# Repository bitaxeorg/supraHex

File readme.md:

> Closed Source is Antithetical to Bitcoin

# Presenting: The supraHex
supraHex is a follow on to the [bitaxe](https://github.com/skot/bitaxe) that incorporates six BM1368 ASICs from the Antminer S21

## Goals
- **Standalone**: can mine directly to your pool over WiFi. No External computer needed.
- **Embedded**: low cost, low maintenance, high availability, high reliability, low power.
- **ASIC**: based on the very efficient BM1368 from Bitmain.
- **Versatile**: solo/pool mining, autotune power/heat/efficiency.
- **Open Source**: All design files are provided.

## Features
- **ESP32-S3-WROOM-1** wifi microcontroller on board
- **TI TPS546D24ARVFR** buck regulator steps down the 12V input to power the chain of BM1368
- **TMP1075** measures inlet and outlet PCB temperature.
- **Microchip EMC2302** Controls dual fans
- Header for optional status LCD
- BAP (Bitaxe Accesory Port)
- ASIC Chip temperature directly from the ASIC's

## BM1368
- The BM1368 is a undocumented SHA256 mining ASIC from Bitmain. It's mostly used in the Antminer S21
- Bitmain claims the BM1368 has 17.5 W/TH efficiency
- The BM1368 is available (new) for around $20~29 each.

## Current Status
- v701 hardware is working! Hash rate is fluctuating between 4 TH/s and 4.2 TH/s.
- Power draw is around 75W @12V.
- ESP32 miner firmware will configure the power supply to run at the proper voltage.
- This is an _advanced_ build! If you don't have experience building boards, you should probably go build a single ASIC bitaxe first to get the technique down.

## Revision List
- V701 is the current working version of this board.  If you want to build this, pull down this git tag.

## Hardware
- [BM1368 from NBTC](https://www.nbtcminer.com/shop/miner-parts/miner-chip/new-bm1368-bm1368pb-for-antminer-s21-t21-hdyro/). The `PB`Variant seems to work fine.
- [Heatsink](https://www.aliexpress.us/item/3256805608902122.html) 90mm long variant. This will need to have threaded M3 mounting holes added. See the KiCad board file for the pattern
- [Fans](https://www.amazon.com/Noctua-NF-A8-PWM-Premium-Quiet/dp/B00NEMG62M) At least one 80x80mm 12V 4-pin fan. Like the Noctua NF-A8 PWM. Possibly two.
- [Enclosure](https://www.aliexpress.us/item/3256806064761702.html) (several sellers) 130mm long variant. The supraHex needs to be run inside an enclosure to force air through the heatsink and effectively cool the BM1368s
- All of the parts on the board are listed in the KiCad BOM

## Software
- [ESP-Miner-Multichip](https://github.com/bitaxeorg/esp-miner-multichip) is still being updated to support multiple ASICs

## Power Supply Requirements
- supraHex takes 12V DC input via screw terminals. Power supply should be capable of 100W
  - This [120W Brick](https://www.amazon.com/gp/product/B07PWZQ33N) technically works, but gets a little warmer than it should. You'll need to change the end.
  - 12V 15A 110V AliExpress [Bare PSU](https://www.aliexpress.us/item/3256805439916551.html)

## Building
- Check out [building.md](building.md) for PCB ordering tips
- Check out [assembly.md](assembly.md) for assembly tips

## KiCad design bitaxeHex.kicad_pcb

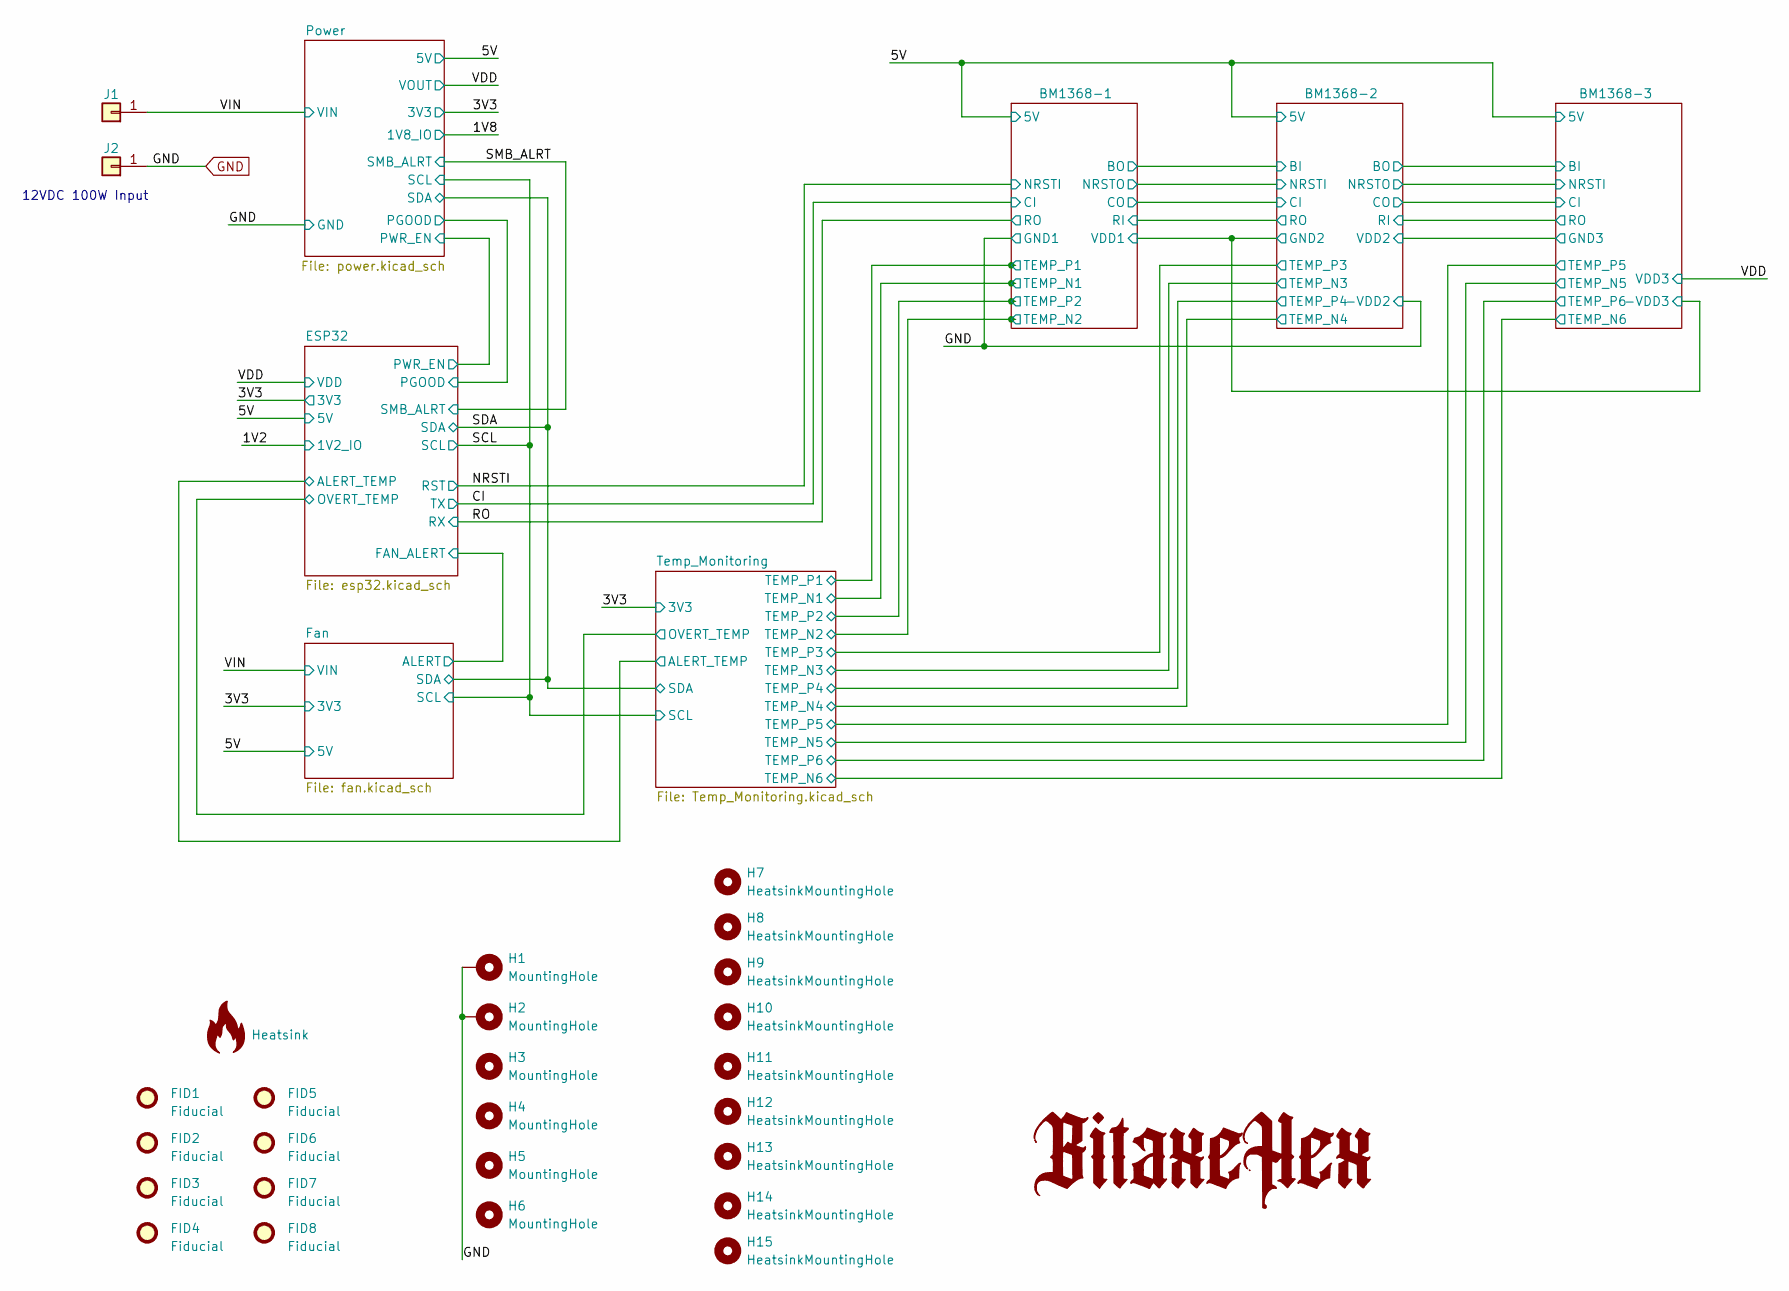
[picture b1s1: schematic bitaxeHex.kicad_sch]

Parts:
FID1, FID2, FID3, FID4, FID5, FID6, FID7, FID8: Fiducial; Fiducial_1mm_Mask2mm
H1, H2, H3, H4, H5, H6: MountingHole; MountingHole_3mm_Pad_Via
H7, H8, H9, H10, H11, H12, H13, H14, H15: HeatsinkMountingHole; 3.1mm_mounting
HS1: Heatsink; hex-heatsink
J1, J2: Screw Terminal; 7771-screw-terminal; PARTNO 36-7771

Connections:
/VIN: J1.1; also elsewhere on the board
GND: H1.1, H2.1, J2.1; also elsewhere on the board

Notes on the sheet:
12VDC 100W Input

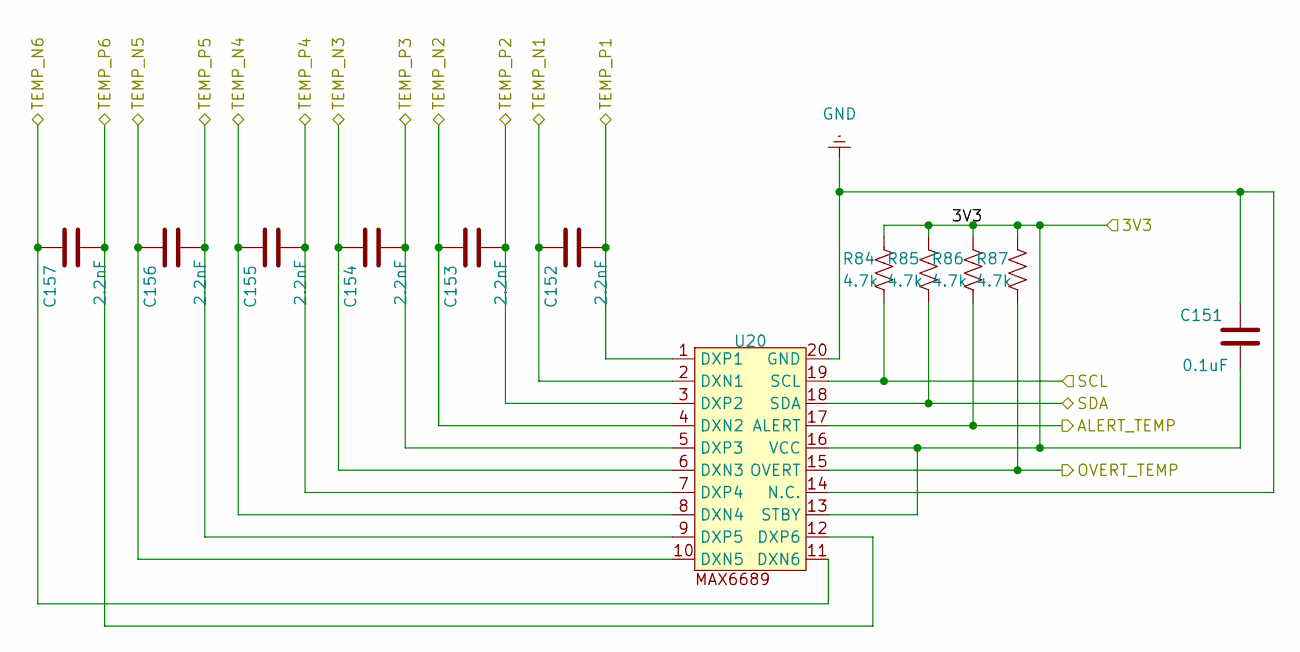
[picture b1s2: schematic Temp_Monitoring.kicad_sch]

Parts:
C151: 0.1uF; C_0402_1005Metric; PARTNO KGM05AR71C104KH
C152, C153, C154, C155, C156, C157: 2.2nF; C_0402_1005Metric; PARTNO CC0402KRX7R9BB222
R84, R85, R86, R87: 4.7k; R_0402_1005Metric; PARTNO RT0402BRD074K7L
U20: MAX6689UP9A+; PARTNO MAX6689UP9A+

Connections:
/3V3: C151.1, R84.2, R85.2, R86.2, R87.2, U20.13 (STBY), U20.16 (VCC); also elsewhere on the board
/BM1368-1/TEMP_N1: C152.2, U20.2 (DXN1); also elsewhere on the board
/BM1368-1/TEMP_N2: C153.2, U20.4 (DXN2); also elsewhere on the board
/BM1368-1/TEMP_P1: C152.1, U20.1 (DXP1); also elsewhere on the board
/BM1368-1/TEMP_P2: C153.1, U20.3 (DXP2); also elsewhere on the board
/BM1368-2/TEMP_N3: C154.2, U20.6 (DXN3); also elsewhere on the board
/BM1368-2/TEMP_N4: C155.2, U20.8 (DXN4); also elsewhere on the board
/BM1368-2/TEMP_P3: C154.1, U20.5 (DXP3); also elsewhere on the board
/BM1368-2/TEMP_P4: C155.1, U20.7 (DXP4); also elsewhere on the board
/BM1368-3/TEMP_N5: C156.2, U20.10 (DXN5); also elsewhere on the board
/BM1368-3/TEMP_N6: C157.2, U20.11 (DXN6); also elsewhere on the board
/BM1368-3/TEMP_P5: C156.1, U20.9 (DXP5); also elsewhere on the board
/BM1368-3/TEMP_P6: C157.1, U20.12 (DXP6); also elsewhere on the board
/ESP32/ALERT_TEMP: R86.1, U20.17 (ALERT); also elsewhere on the board
/ESP32/OVERT_TEMP: R87.1, U20.15 (OVERT); also elsewhere on the board
/SCL: R84.1, U20.19 (SCL); also elsewhere on the board
/SDA: R85.1, U20.18 (SDA); also elsewhere on the board
GND: C151.2, U20.14 (N.C.), U20.20 (GND); also elsewhere on the board

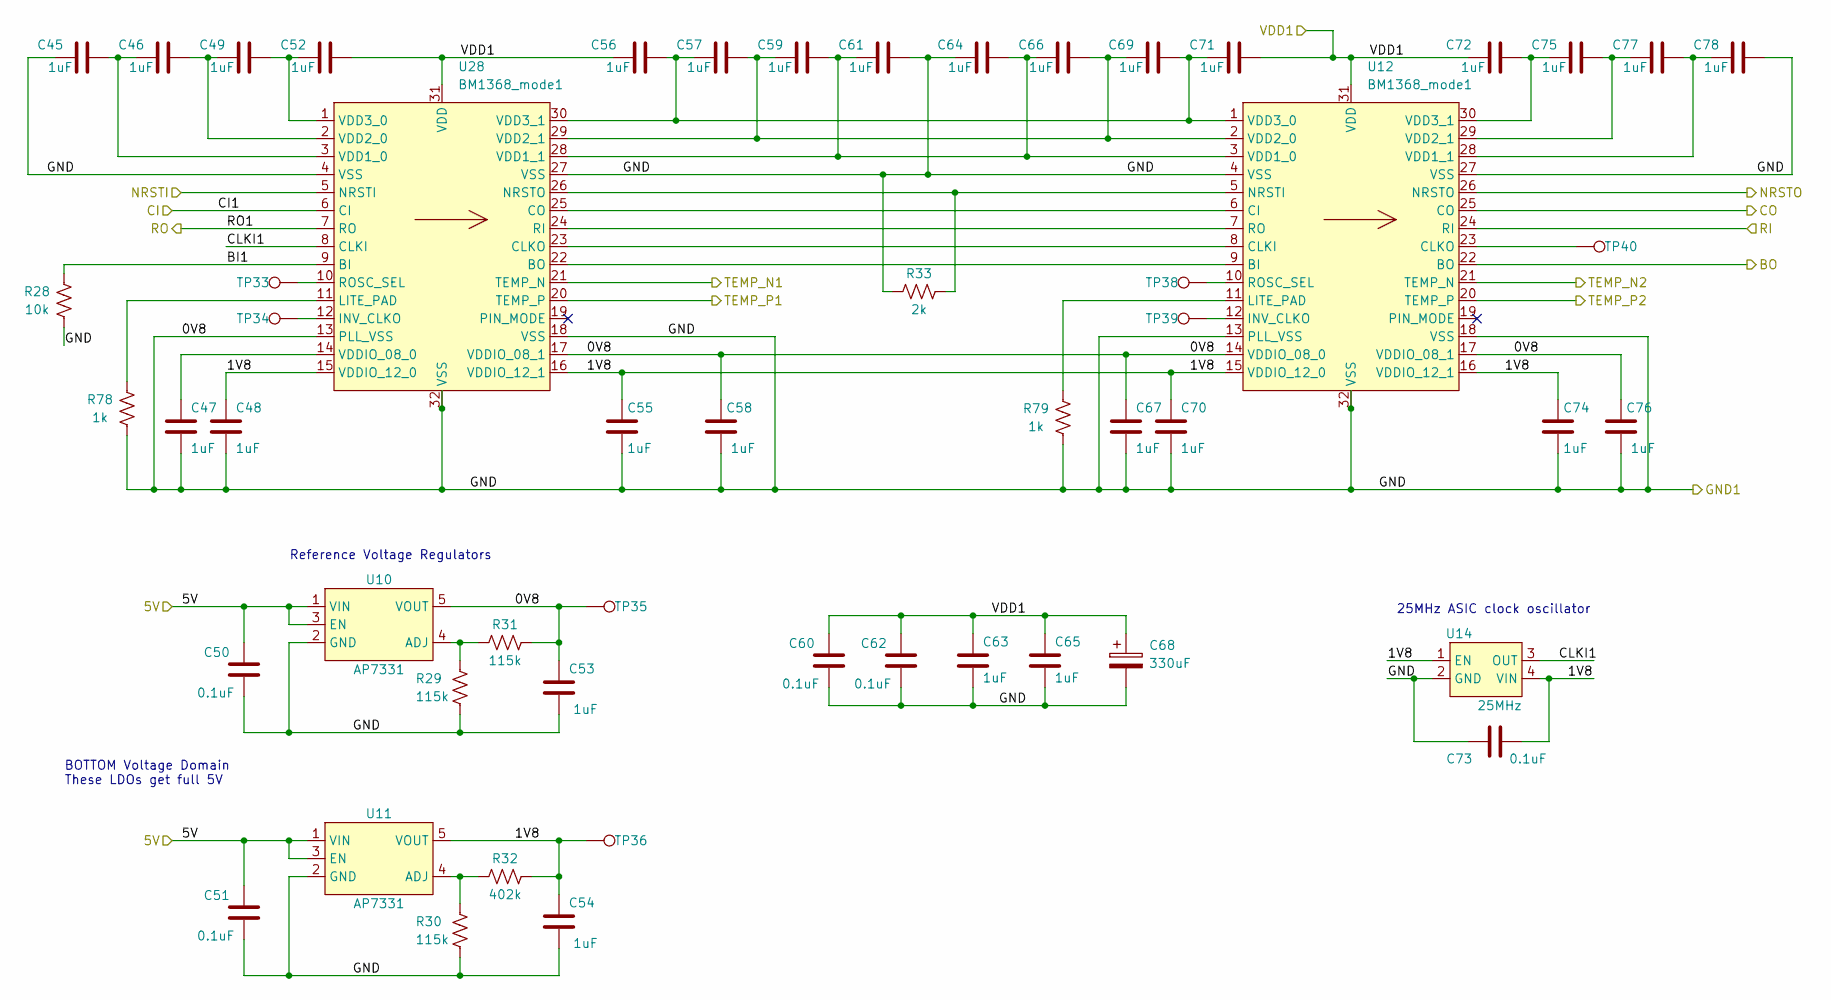
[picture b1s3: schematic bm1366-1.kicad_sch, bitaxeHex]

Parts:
C45, C46, C47, C48, C49, C52, C53, C54, C55, C56, C57, C58, C59, C61, C63, C64, C65, C66, C67, C69, C70, C71, C72, C74, C75, C76, C77, C78: 1uF; C_0402_1005Metric; PARTNO EMK105BJ105MV-F
C50, C51, C60, C62, C73: 0.1uF; C_0402_1005Metric; PARTNO KGM05AR71C104KH
C68: 330uF; CP_EIA-7343-31_Kemet-D_Pad2.25x2.55mm_HandSolder; PARTNO 293D337X9010E2TE3
R28: 10k; R_0402_1005Metric; PARTNO RC0402JR-0710KL
R29, R30, R31: 115k; R_0402_1005Metric; PARTNO RC0402FR-07115KL
R32: 402k; R_0402_1005Metric; PARTNO RC0402FR-07402KL
R33: 2k; R_0402_1005Metric; PARTNO RT0402BRD072KL
R78, R79: 1k; R_0402_1005Metric; PARTNO RC0402FR-071KL
TP33, TP34, TP35, TP36, TP38, TP39, TP40: TestPoint; TestPoint_Pad_D1.0mm
U10, U11: AP7331; TSOT-23-5; PARTNO AP7331-WG-7
U12, U28: BM1368_mode1; BM1368
U14: 25MHz; O 25,0-JO32-B-1V3-1-T1-LF; PARTNO O 25,0-JO32-B-1V3-1-T1-LF

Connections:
/5V: C50.2, C51.2, U10.1 (VIN), U10.3 (EN), U11.1 (VIN), U11.3 (EN); also elsewhere on the board
/BM1368-1/1V8: C48.1, C54.1, C55.1, C70.1, C73.1, C74.1, R32.1, TP36.1, U11.5 (VOUT), U12.15 (VDDIO_12_0), U12.16 (VDDIO_12_1), U14.1 (EN), U14.4 (VIN), U28.15 (VDDIO_12_0), U28.16 (VDDIO_12_1)
/BM1368-1/BI1: R28.2, U28.9 (BI)
/BM1368-1/BO: U12.22 (BO); also elsewhere on the board
/BM1368-1/CLKI1: U14.3 (OUT), U28.8 (CLKI)
/BM1368-1/CO: U12.25 (CO); also elsewhere on the board
/BM1368-1/NRSTO: U12.26 (NRSTO); also elsewhere on the board
/BM1368-1/RI: U12.24 (RI); also elsewhere on the board
/BM1368-1/TEMP_N1: U28.21 (TEMP_N); also elsewhere on the board
/BM1368-1/TEMP_N2: U12.21 (TEMP_N); also elsewhere on the board
/BM1368-1/TEMP_P1: U28.20 (TEMP_P); also elsewhere on the board
/BM1368-1/TEMP_P2: U12.20 (TEMP_P); also elsewhere on the board
/BM1368-1/VDD1: C52.2, C56.1, C60.2, C62.2, C63.1, C65.1, C68.1, C71.2, C72.1, U12.31 (VDD), U28.31 (VDD); also elsewhere on the board
/CI: U28.6 (CI); also elsewhere on the board
/NRSTI: U28.5 (NRSTI); also elsewhere on the board
/RO: U28.7 (RO); also elsewhere on the board
GND: C45.1, C47.2, C48.2, C50.1, C51.1, C53.1, C53.2, C54.2, C55.2, C58.1, C58.2, C60.1, C61.2, C62.1, C63.2, C64.1, C65.2, C67.1, C67.2, C68.2, C70.2, C73.2, C74.2, C76.1, C76.2, C78.2, R28.1, R29.1, R30.1, R31.2, R33.1, R78.1, R79.1, TP35.1, U10.2 (GND), U10.5 (VOUT), U11.2 (GND), U12.4 (VSS), U12.13 (PLL_VSS), U12.14 (VDDIO_08_0), U12.17 (VDDIO_08_1), U12.18 (VSS), U12.27 (VSS), U12.32 (VSS), U14.2 (GND), U28.4 (VSS), U28.13 (PLL_VSS), U28.17 (VDDIO_08_1), U28.18 (VSS), U28.27 (VSS), U28.32 (VSS); also elsewhere on the board
unnamed: R29.2, R31.1, U10.4 (ADJ)
unnamed: R30.2, R32.2, U11.4 (ADJ)
unnamed: U12.9 (BI), U28.22 (BO)
unnamed: U12.6 (CI), U28.25 (CO)
unnamed: U12.8 (CLKI), U28.23 (CLKO)
unnamed: TP40.1, U12.23 (CLKO)
unnamed: TP39.1, U12.12 (INV_CLKO)
unnamed: R79.2, U12.11 (LITE_PAD)
unnamed: R33.2, U12.5 (NRSTI), U28.26 (NRSTO)
unnamed: U12.7 (RO), U28.24 (RI)
unnamed: TP38.1, U12.10 (ROSC_SEL)
unnamed: C59.2, C61.1, C64.2, C66.1, U12.3 (VDD1_0), U28.28 (VDD1_1)
unnamed: C77.2, C78.1, U12.28 (VDD1_1)
unnamed: C57.2, C59.1, C66.2, C69.1, U12.2 (VDD2_0), U28.29 (VDD2_1)
unnamed: C75.2, C77.1, U12.29 (VDD2_1)
unnamed: C56.2, C57.1, C69.2, C71.1, U12.1 (VDD3_0), U28.30 (VDD3_1)
unnamed: C72.2, C75.1, U12.30 (VDD3_1)
unnamed: TP34.1, U28.12 (INV_CLKO)
unnamed: R78.2, U28.11 (LITE_PAD)
unnamed: TP33.1, U28.10 (ROSC_SEL)
unnamed: C45.2, C46.1, U28.3 (VDD1_0)
unnamed: C46.2, C49.1, U28.2 (VDD2_0)
unnamed: C49.2, C52.1, U28.1 (VDD3_0)
unnamed: C47.1, U28.14 (VDDIO_08_0)

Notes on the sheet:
Reference Voltage Regulators
BOTTOM Voltage Domain These LDOs get full 5V
25MHz ASIC clock oscillator

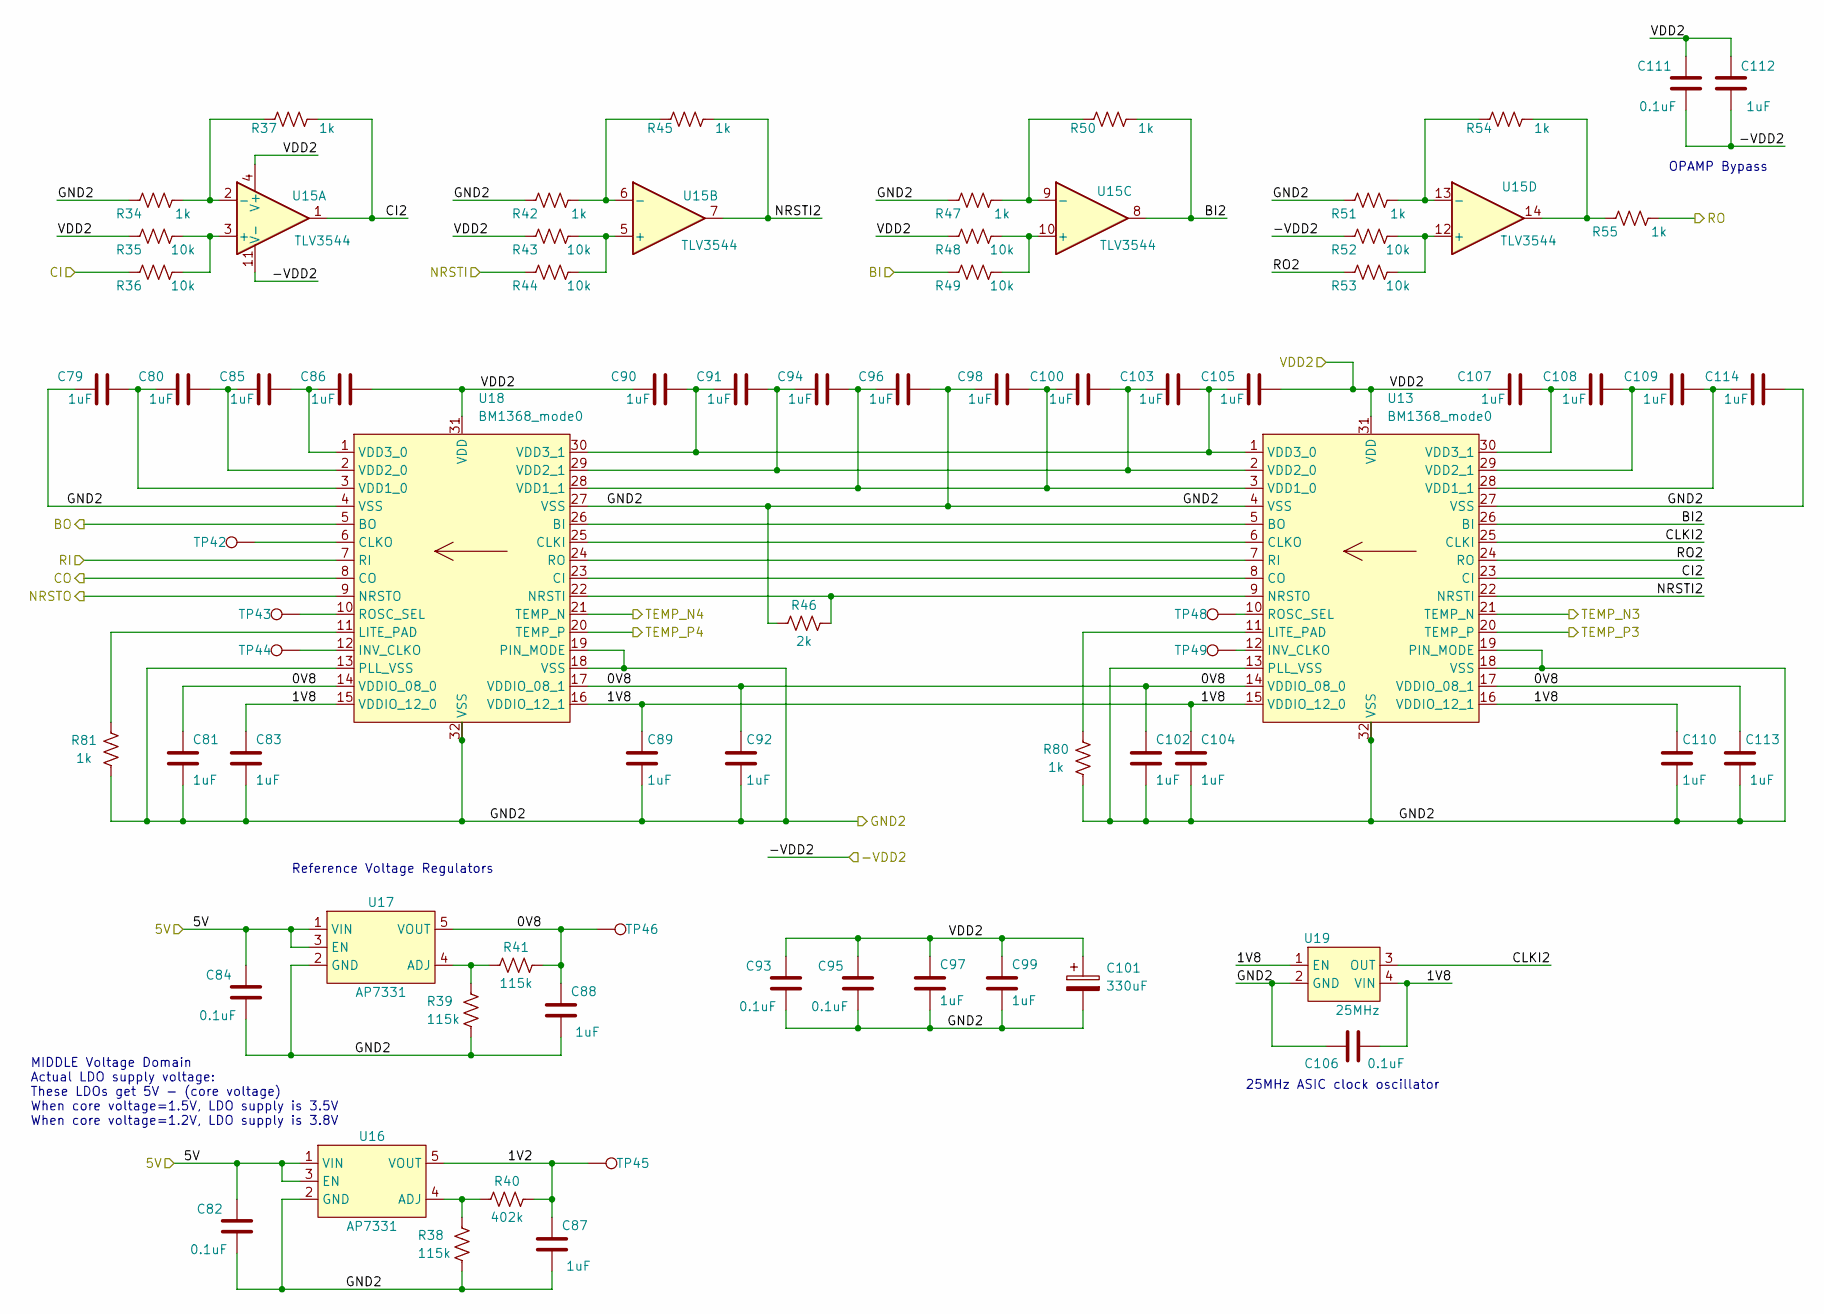
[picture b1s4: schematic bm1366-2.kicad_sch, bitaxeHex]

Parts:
C79, C80, C81, C83, C85, C86, C87, C88, C89, C90, C91, C92, C94, C96, C97, C98, C99, C100, C102, C103, C104, C105, C107, C108, C109, C110, C112, C113, C114: 1uF; C_0402_1005Metric; PARTNO EMK105BJ105MV-F
C82, C84, C93, C95, C106, C111: 0.1uF; C_0402_1005Metric; PARTNO KGM05AR71C104KH
C101: 330uF; CP_EIA-7343-31_Kemet-D_Pad2.25x2.55mm_HandSolder; PARTNO 293D337X9010E2TE3
R34, R37, R42, R45, R47, R50, R51, R54, R55, R80, R81: 1k; R_0402_1005Metric; PARTNO RC0402FR-071KL
R35, R36, R43, R44, R48, R49, R52, R53: 10k; R_0402_1005Metric; PARTNO RC0402JR-0710KL
R38, R39, R41: 115k; R_0402_1005Metric; PARTNO RC0402FR-07115KL
R40: 402k; R_0402_1005Metric; PARTNO RC0402FR-07402KL
R46: 2k; R_0402_1005Metric; PARTNO RT0402BRD072KL
TP42, TP43, TP44, TP45, TP46, TP48, TP49: TestPoint; TestPoint_Pad_D1.0mm
U13, U18: BM1368_mode0; BM1368
U15: TLV3544; TSSOP-14_4.4x5mm_P0.65mm; PARTNO TLV3544IPWR
U16, U17: AP7331; TSOT-23-5; PARTNO AP7331-WG-7
U19: 25MHz; O 25,0-JO32-B-1V3-1-T1-LF; PARTNO O 25,0-JO32-B-1V3-1-T1-LF

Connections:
/5V: C82.2, C84.2, U16.1 (VIN), U16.3 (EN), U17.1 (VIN), U17.3 (EN); also elsewhere on the board
/BM1368-1/BO: R49.1; also elsewhere on the board
/BM1368-1/CO: R36.1; also elsewhere on the board
/BM1368-1/NRSTO: R44.1; also elsewhere on the board
/BM1368-1/RI: R55.1; also elsewhere on the board
/BM1368-1/VDD1: C79.1, C81.2, C82.1, C83.2, C84.1, C87.2, C88.2, C89.2, C92.2, C93.1, C95.1, C96.2, C97.2, C98.1, C99.2, C101.2, C102.2, C104.2, C106.2, C110.2, C113.2, C114.2, R34.2, R38.1, R39.1, R42.2, R46.1, R47.2, R51.2, R80.1, R81.1, U13.4 (VSS), U13.13 (PLL_VSS), U13.18 (VSS), U13.19 (PIN_MODE), U13.27 (VSS), U13.32 (VSS), U16.2 (GND), U17.2 (GND), U18.4 (VSS), U18.13 (PLL_VSS), U18.18 (VSS), U18.19 (PIN_MODE), U18.27 (VSS), U18.32 (VSS), U19.2 (GND); also elsewhere on the board
/BM1368-2/0V8: C81.1, C88.1, C92.1, C102.1, C113.1, R41.2, TP46.1, U13.14 (VDDIO_08_0), U13.17 (VDDIO_08_1), U17.5 (VOUT), U18.14 (VDDIO_08_0), U18.17 (VDDIO_08_1)
/BM1368-2/BI2: R50.1, U13.26 (BI), U15.8
/BM1368-2/BO: U18.5 (BO); also elsewhere on the board
/BM1368-2/CI2: R37.1, U13.23 (CI), U15.1
/BM1368-2/CLKI2: U13.25 (CLKI), U19.3 (OUT)
/BM1368-2/CO: U18.8 (CO); also elsewhere on the board
/BM1368-2/NRSTI2: R45.1, U13.22 (NRSTI), U15.7
/BM1368-2/NRSTO: U18.9 (NRSTO); also elsewhere on the board
/BM1368-2/RI: U18.7 (RI); also elsewhere on the board
/BM1368-2/RO2: R53.1, U13.24 (RO)
/BM1368-2/TEMP_N3: U13.21 (TEMP_N); also elsewhere on the board
/BM1368-2/TEMP_N4: U18.21 (TEMP_N); also elsewhere on the board
/BM1368-2/TEMP_P3: U13.20 (TEMP_P); also elsewhere on the board
/BM1368-2/TEMP_P4: U18.20 (TEMP_P); also elsewhere on the board
/BM1368-2/VDD2: C86.2, C90.1, C93.2, C95.2, C97.1, C99.1, C101.1, C105.2, C107.1, C111.2, C112.2, R35.2, R43.1, R48.1, U13.31 (VDD), U15.4 (V+), U18.31 (VDD); also elsewhere on the board
GND: C111.1, C112.1, R52.1, U15.11 (V-); also elsewhere on the board
unnamed: R54.1, R55.2, U15.14
unnamed: U13.5 (BO), U18.26 (BI)
unnamed: U13.6 (CLKO), U18.25 (CLKI)
unnamed: U13.8 (CO), U18.23 (CI)
unnamed: TP49.1, U13.12 (INV_CLKO)
unnamed: R80.2, U13.11 (LITE_PAD)
unnamed: R46.2, U13.9 (NRSTO), U18.22 (NRSTI)
unnamed: U13.7 (RI), U18.24 (RO)
unnamed: TP48.1, U13.10 (ROSC_SEL)
unnamed: C94.2, C96.1, C98.2, C100.1, U13.3 (VDD1_0), U18.28 (VDD1_1)
unnamed: C109.2, C114.1, U13.28 (VDD1_1)
unnamed: C91.2, C94.1, C100.2, C103.1, U13.2 (VDD2_0), U18.29 (VDD2_1)
unnamed: C108.2, C109.1, U13.29 (VDD2_1)
unnamed: C90.2, C91.1, C103.2, C105.1, U13.1 (VDD3_0), U18.30 (VDD3_1)
unnamed: C107.2, C108.1, U13.30 (VDD3_1)
unnamed: R35.1, R36.2, U15.3 (+)
unnamed: R34.1, R37.2, U15.2 (-)
unnamed: R43.2, R44.2, U15.5 (+)
unnamed: R42.1, R45.2, U15.6 (-)
unnamed: R48.2, R49.2, U15.10 (+)
unnamed: R47.1, R50.2, U15.9 (-)
unnamed: R52.2, R53.2, U15.12 (+)
unnamed: R51.1, R54.2, U15.13 (-)
unnamed: R38.2, R40.2, U16.4 (ADJ)
unnamed: R39.2, R41.1, U17.4 (ADJ)
unnamed: TP42.1, U18.6 (CLKO)
unnamed: TP44.1, U18.12 (INV_CLKO)
unnamed: R81.2, U18.11 (LITE_PAD)
unnamed: TP43.1, U18.10 (ROSC_SEL)
unnamed: C79.2, C80.1, U18.3 (VDD1_0)
unnamed: C80.2, C85.1, U18.2 (VDD2_0)
unnamed: C85.2, C86.1, U18.1 (VDD3_0)

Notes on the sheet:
MIDDLE Voltage Domain Actual LDO supply voltage: These LDOs get 5V - (core voltage) When core voltage=1.5V, LDO supply is 3.5V When core voltage=1.2V, LDO supply is 3.8V
Reference Voltage Regulators
25MHz ASIC clock oscillator
OPAMP Bypass

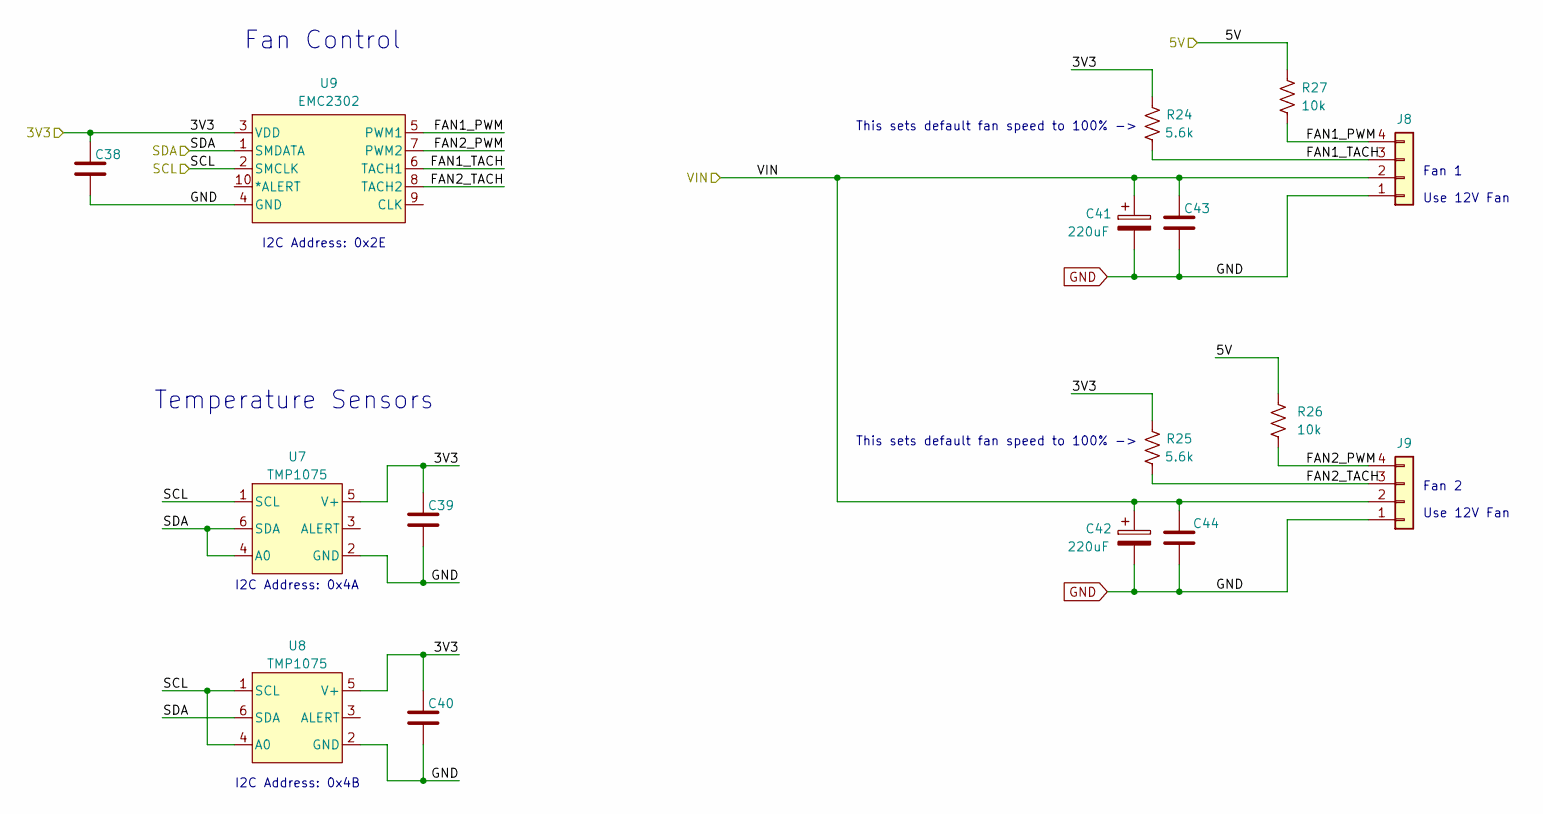
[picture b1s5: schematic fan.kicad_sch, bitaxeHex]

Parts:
C38, C39, C40, C43, C44: 311-3342-1-ND; C_0402_1005Metric; PARTNO KGM05AR71C104KH
C41, C42: 220uF; CP_Elec_6.3x7.7; PARTNO 865080345012
J8, J9: Conn_01x04; 470531000; PARTNO 0470531000
R24, R25: 5.6k; R_0402_1005Metric; PARTNO RC0402FR-135K6L
R26, R27: 10k; R_0402_1005Metric; PARTNO RC0402JR-0710KL
U7, U8: TMP1075; SOT5X3-6_DRL_TEX; PARTNO TMP1075NDRLR
U9: EMC2302; MSOP-10_3x3mm_P0.5mm; PARTNO EMC2302-2-AIZL-TR

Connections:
/3V3: C38.1, C39.1, C40.1, R24.2, R25.2, U7.5 (V+), U8.5 (V+), U9.3 (VDD); also elsewhere on the board
/5V: R26.2, R27.2; also elsewhere on the board
/Fan/FAN1_PWM: J8.4, R27.1, U9.5 (PWM1)
/Fan/FAN1_TACH: J8.3, R24.1, U9.6 (TACH1)
/Fan/FAN2_PWM: J9.4, R26.1, U9.7 (PWM2)
/Fan/FAN2_TACH: J9.3, R25.1, U9.8 (TACH2)
/SCL: U7.1 (SCL), U8.1 (SCL), U8.4 (A0), U9.2 (SMCLK); also elsewhere on the board
/SDA: U7.4 (A0), U7.6 (SDA), U8.6 (SDA), U9.1 (SMDATA); also elsewhere on the board
/VIN: C41.1, C42.1, C43.1, C44.1, J8.2, J9.2; also elsewhere on the board
GND: C38.2, C39.2, C40.2, C41.2, C42.2, C43.2, C44.2, J8.1, J9.1, U7.2 (GND), U8.2 (GND), U9.4 (GND); also elsewhere on the board

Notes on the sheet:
I2C Address: 0x2E
Temperature Sensors
I2C Address: 0x4A
Fan Control
Fan 1
Use 12V Fan
This sets default fan speed to 100% ->
Fan 2
I2C Address: 0x4B

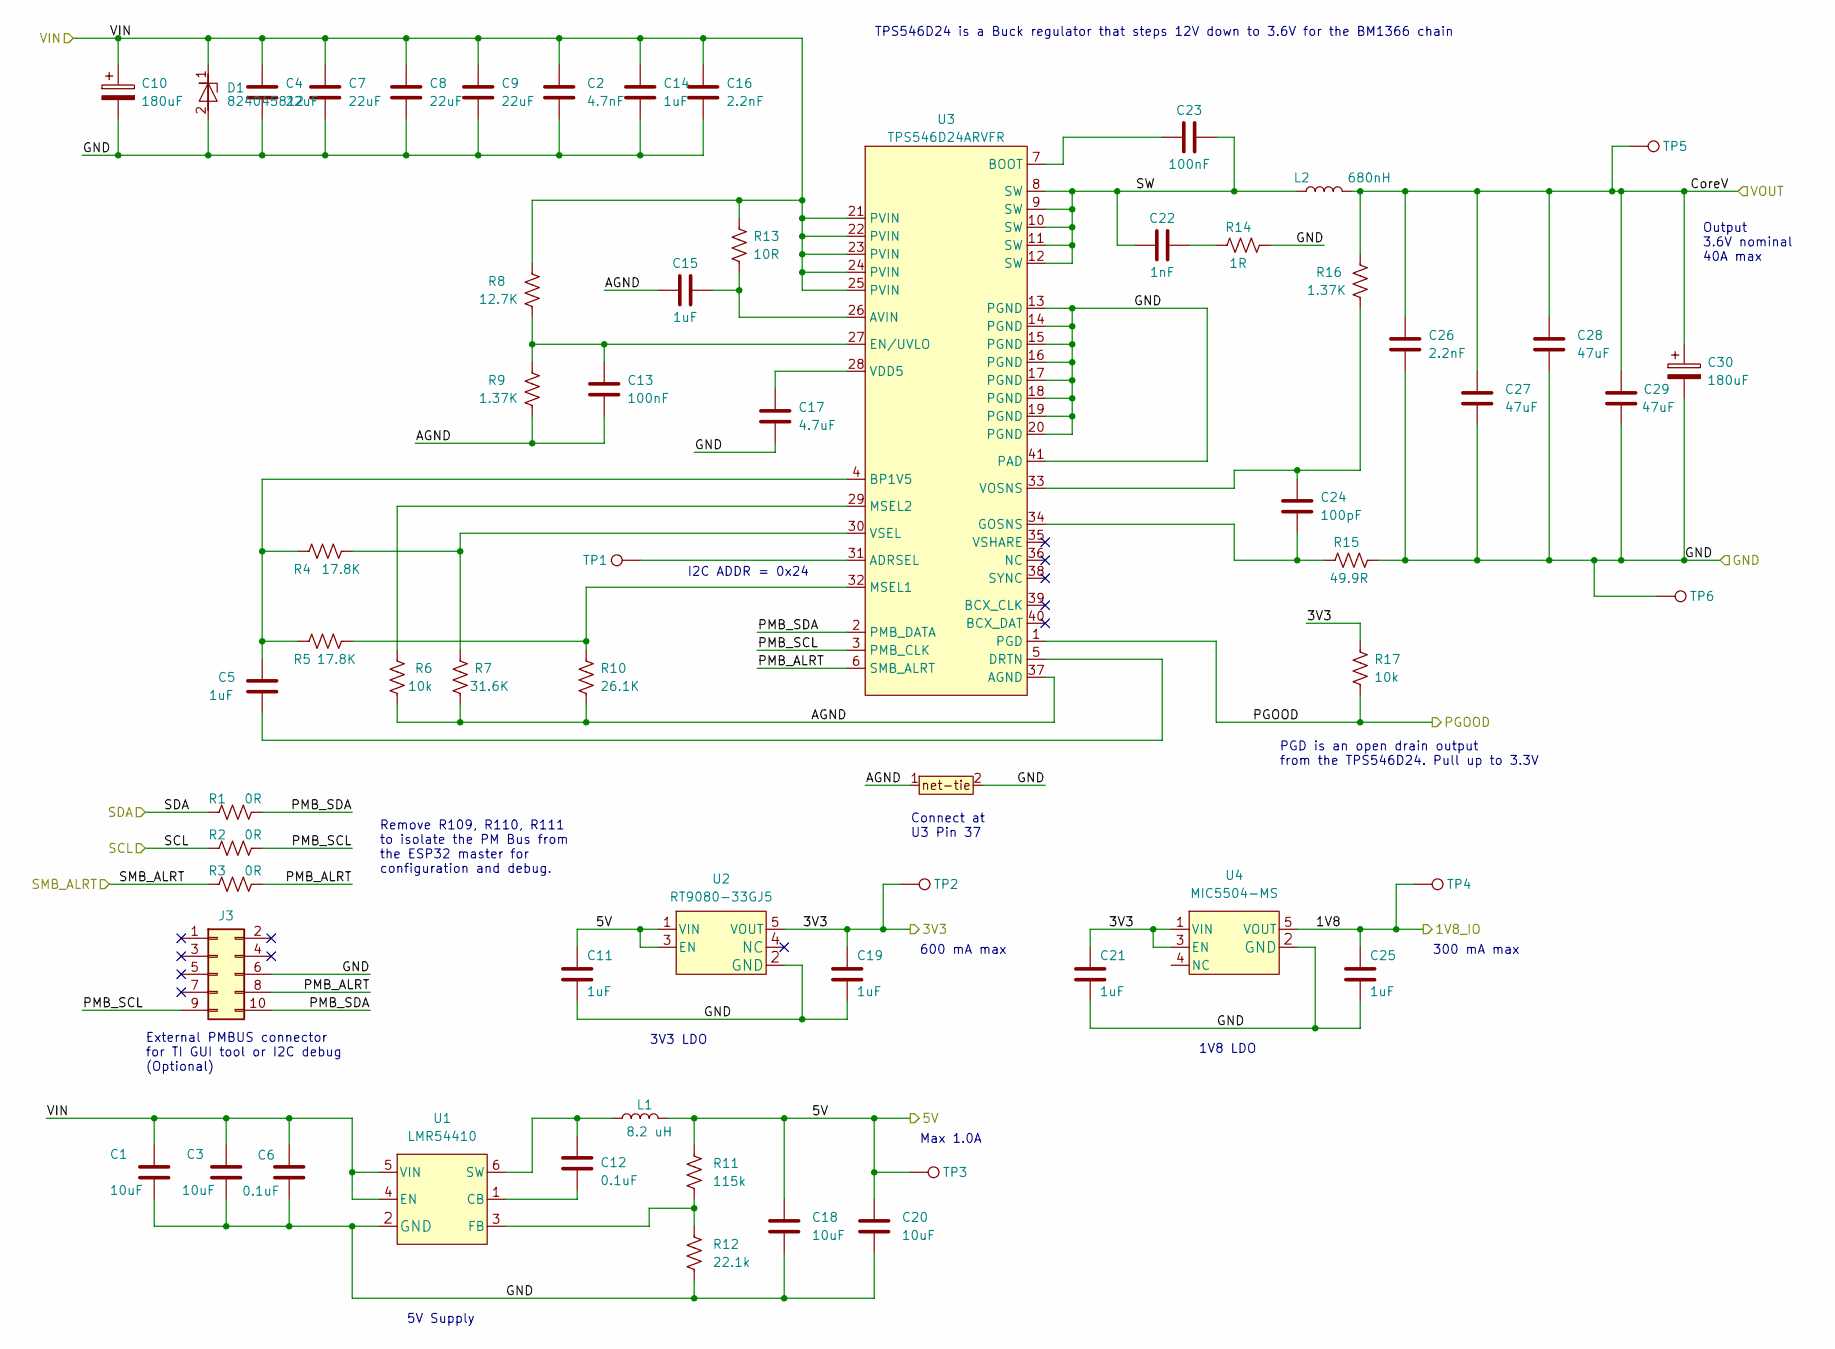
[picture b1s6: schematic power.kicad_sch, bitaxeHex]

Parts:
C1, C3, C18, C20: 10uF; C_0805_2012Metric; PARTNO GRM21BR61H106ME43L
C2: 4.7nF; C_0402_1005Metric; PARTNO GRM155R71E472KA01D
C4, C7, C8, C9: 22uF; C_1210_3225Metric; PARTNO GRM32ER61E226KE15L
C5: 1uF; C_0603_1608Metric; PARTNO GRM188R60J105KA01D
C6: 0.1uF; C_0603_1608Metric; PARTNO KGM15BR71H104KT
C10, C30: 180uF; CP_Elec_6.3x5.9; PARTNO 16SVPF180M
C11, C19, C21, C25: 1uF; C_0402_1005Metric; PARTNO EMK105BJ105MV-F
C12: 0.1uF; C_0402_1005Metric; PARTNO KGM05AR71C104KH
C13: 100nF; C_0402_1005Metric; PARTNO GRM155R71A104KA01D
C14, C15: 1uF; C_0805_2012Metric; PARTNO TMK212BJ105KG-T
C16, C26: 2.2nF; C_0402_1005Metric; PARTNO GRM155R61H222KA01D
C17: 4.7uF; C_0402_1005Metric; PARTNO GRM155R61A475MEAAD
C22: 1nF; C_0805_2012Metric; PARTNO CC0805KRX7R9BB102
C23: 100nF; C_0805_2012Metric; PARTNO KGM21NR71E104KT
C24: 100pF; C_0402_1005Metric; PARTNO 885012005013
C27, C28, C29: 47uF; C_1210_3225Metric; PARTNO GRM32ER61C476KE15L
D1: 824045812; PARTNO 824045812
J3: Conn_02x05_Odd_Even; PinHeader_2x05_P2.54mm_Vertical
L1: 8.2 uH; 74438357082; PARTNO 78438357082
L2: 680nH; L_Coilcraft_XAL1010-XXX; PARTNO XAL1010-681MED; Mouser 994-XAL1010-681MED
R1, R2, R3: 0R; R_0402_1005Metric; PARTNO RC0402JR-070RL
R4, R5: 17.8K; R_0402_1005Metric; PARTNO RMCF0402FT17K8
R6: 10k; R_0402_1005Metric; PARTNO RMCF0402FT10K0
R7: 31.6K; R_0402_1005Metric; PARTNO RC0402FR-0731K6L
R8: 12.7K; R_0402_1005Metric; PARTNO RC0402FR-0712K7L
R9, R16: 1.37K; R_0402_1005Metric; PARTNO RC0402FR-071K37L
R10: 26.1K; R_0402_1005Metric; PARTNO RC0402FR-0726K1L
R11: 115k; R_0402_1005Metric; PARTNO RC0402FR-07115KL
R12: 22.1k; R_0402_1005Metric; PARTNO RC0402FR-0722K1L
R13: 10R; R_0402_1005Metric; PARTNO RC0402FR-0710RL
R14: 1R; R_1206_3216Metric; PARTNO CSR1206FT1R00
R15: 49.9R; R_0402_1005Metric; PARTNO RC0402FR-0749R9L
R17: 10k; R_0402_1005Metric; PARTNO RC0402JR-0710KL
T1: net-tie; Net-Tie-0.25mm
TP1: TestPoint; TestPoint_Pad_D0.8mm
TP2, TP3, TP4, TP5, TP6: TestPoint; TestPoint_Pad_D1.0mm
U1: LMR54410; SOT-23-6; PARTNO LMR54410FDBVR
U2: RT9080-33GJ5; PARTNO RT9080-33GJ5
U3: TPS546D24ARVFR; LQFN40-CLIP; PARTNO TPS546D24ARVFR
U4: MIC5504-MS; SOT-23-5_HandSoldering; PARTNO MIC5504-1.8YM5-TR

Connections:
/1V8: C25.1, TP4.1, U4.5 (VOUT)
/3V3: C19.1, C21.1, R17.2, TP2.1, U2.5 (VOUT), U4.1 (VIN), U4.3 (EN); also elsewhere on the board
/5V: C11.1, C18.1, C20.1, L1.2, R11.1, TP3.1, U2.1 (VIN), U2.3 (EN); also elsewhere on the board
/Power/AGND: C13.2, C15.1, R6.1, R7.2, R9.2, R10.2, T1.1, U3.37 (AGND)
/Power/PGOOD: R17.1, U3.1 (PGD); also elsewhere on the board
/Power/PMB_ALRT: J3.8, R3.2, U3.6 (SMB_ALRT)
/Power/PMB_SCL: J3.9, R2.2, U3.3 (PMB_CLK)
/Power/PMB_SDA: J3.10, R1.2, U3.2 (PMB_DATA)
/Power/SW: C22.1, C23.2, L2.1, U3.8 (SW), U3.9 (SW), U3.10 (SW), U3.11 (SW), U3.12 (SW)
/SCL: R2.1; also elsewhere on the board
/SDA: R1.1; also elsewhere on the board
/SMB_ALRT: R3.1; also elsewhere on the board
/VDD: C26.1, C27.1, C28.1, C29.1, C30.1, L2.2, R16.1, TP5.1; also elsewhere on the board
/VIN: C1.1, C2.1, C3.1, C4.1, C6.2, C7.1, C8.1, C9.1, C10.1, C14.1, C16.1, D1.1 (I/O), R8.1, R13.1, U1.4 (EN), U1.5 (VIN), U3.21 (PVIN), U3.22 (PVIN), U3.23 (PVIN), U3.24 (PVIN), U3.25 (PVIN); also elsewhere on the board
GND: C1.2, C2.2, C3.2, C4.2, C6.1, C7.2, C8.2, C9.2, C10.2, C11.2, C14.2, C16.2, C17.2, C18.2, C19.2, C20.2, C21.2, C25.2, C26.2, C27.2, C28.2, C29.2, C30.2, D1.2 (GND), J3.6, R12.2, R14.2, R15.2, TP6.1, U1.2 (GND), U2.2 (GND), U3.13 (PGND), U3.14 (PGND), U3.15 (PGND), U3.16 (PGND), U3.17 (PGND), U3.18 (PGND), U3.19 (PGND), U3.20 (PGND), U3.41 (PAD), U4.2 (GND); also elsewhere on the board
unnamed: C22.2, R14.1
unnamed: C12.2, U1.1 (CB)
unnamed: R11.2, R12.1, U1.3 (FB)
unnamed: C12.1, L1.1, U1.6 (SW)
unnamed: TP1.1, U3.31 (ADRSEL)
unnamed: C15.2, R13.2, U3.26 (AVIN)
unnamed: C23.1, U3.7 (BOOT)
unnamed: C5.1, R4.1, R5.1, U3.4 (BP1V5)
unnamed: C5.2, U3.5 (DRTN)
unnamed: C13.1, R8.2, R9.1, U3.27 (EN/UVLO)
unnamed: C24.2, R15.1, U3.34 (GOSNS)
unnamed: R5.2, R10.1, U3.32 (MSEL1)
unnamed: R6.2, U3.29 (MSEL2)
unnamed: C17.1, U3.28 (VDD5)
unnamed: C24.1, R16.2, U3.33 (VOSNS)
unnamed: R4.2, R7.1, U3.30 (VSEL)

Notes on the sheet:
1V8 LDO
Output 3.6V nominal 40A max
TPS546D24 is a Buck regulator that steps 12V down to 3.6V for the BM1366 chain
3V3 LDO
300 mA max
Remove R109, R110, R111 to isolate the PM Bus from the ESP32 master for configuration and debug.
Max 1.0A
Connect at U3 Pin 37
External PMBUS connector for TI GUI tool or I2C debug (Optional)
600 mA max
5V Supply
PGD is an open drain output from the TPS546D24. Pull up to 3.3V
I2C ADDR = 0x24
